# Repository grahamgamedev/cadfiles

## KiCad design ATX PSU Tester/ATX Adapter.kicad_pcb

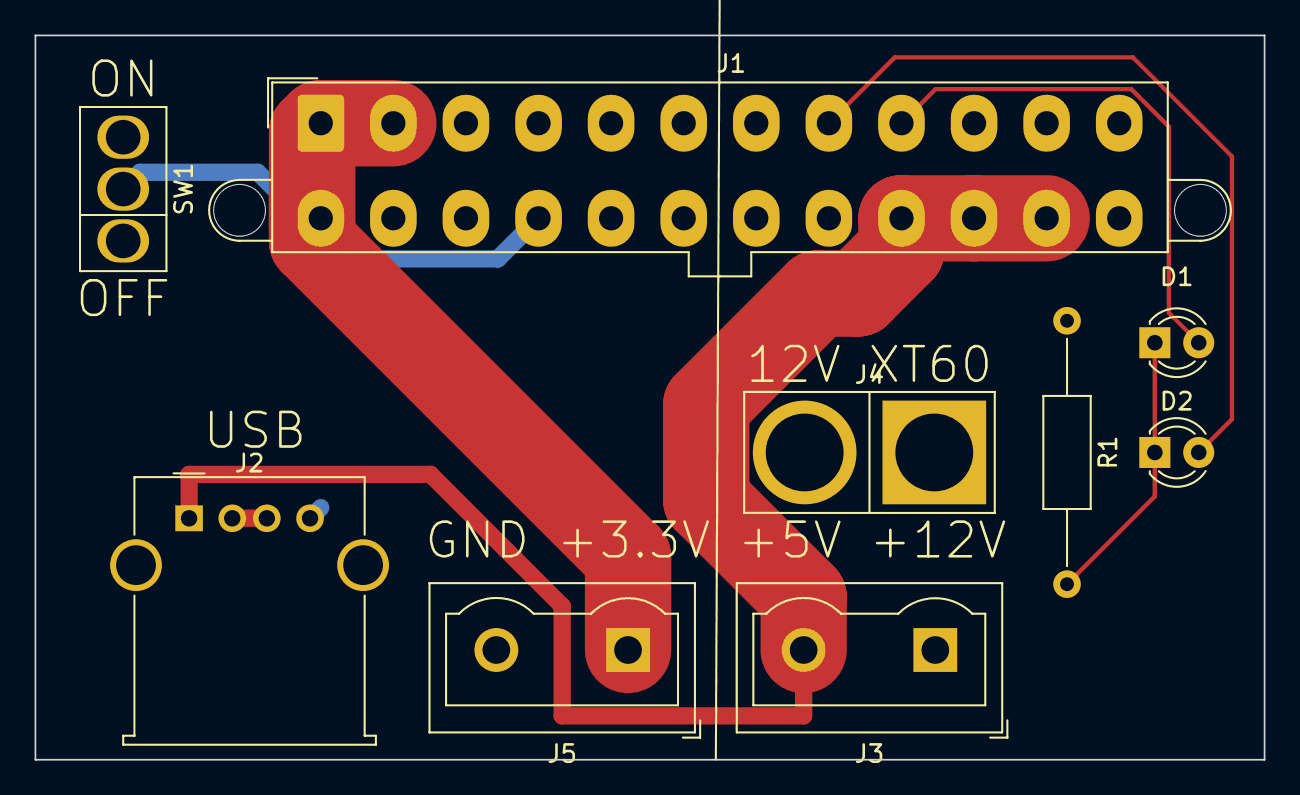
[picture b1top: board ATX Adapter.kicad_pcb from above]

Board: 2 copper layers, 71.1 x 41.9 mm, 9 parts (0 on the bottom side), 9 nets.

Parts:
D1, D2: LED; LED_D3.0mm
J1: ATX-24; Molex_Mini-Fit_Jr_5566-24A2_2x12_P4.20mm_Vertical
J2: USB_A; USB_A_Molex_67643_Horizontal
J3, J5: Screw_Terminal_01x02; TerminalBlock_Wuerth_691311400102_P7.62mm
J4: Conn_01x02; XT60
R1: R; R_Axial_DIN0207_L6.3mm_D2.5mm_P15.24mm_Horizontal
SW1: SW_SPDT; Toggle_Switch_THT

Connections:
unnamed: D1.1, D2.1, R1.2
unnamed: D1.2, J1.9
unnamed: D2.2, J1.8
unnamed: J1.1, J1.2, J1.12, J1.13, J5.1
unnamed: J1.10, J1.11, J3.1, J4.1
unnamed: J1.3, J1.5, J1.7, J1.15, J1.17, J1.18, J1.19, J1.24, J2.4, J2.5, J4.2, J5.2, R1.1, SW1.1
unnamed: J1.16, SW1.2
unnamed: J1.4, J1.6, J1.21, J1.22, J1.23, J2.1, J3.2
unnamed: J2.2, J2.3
